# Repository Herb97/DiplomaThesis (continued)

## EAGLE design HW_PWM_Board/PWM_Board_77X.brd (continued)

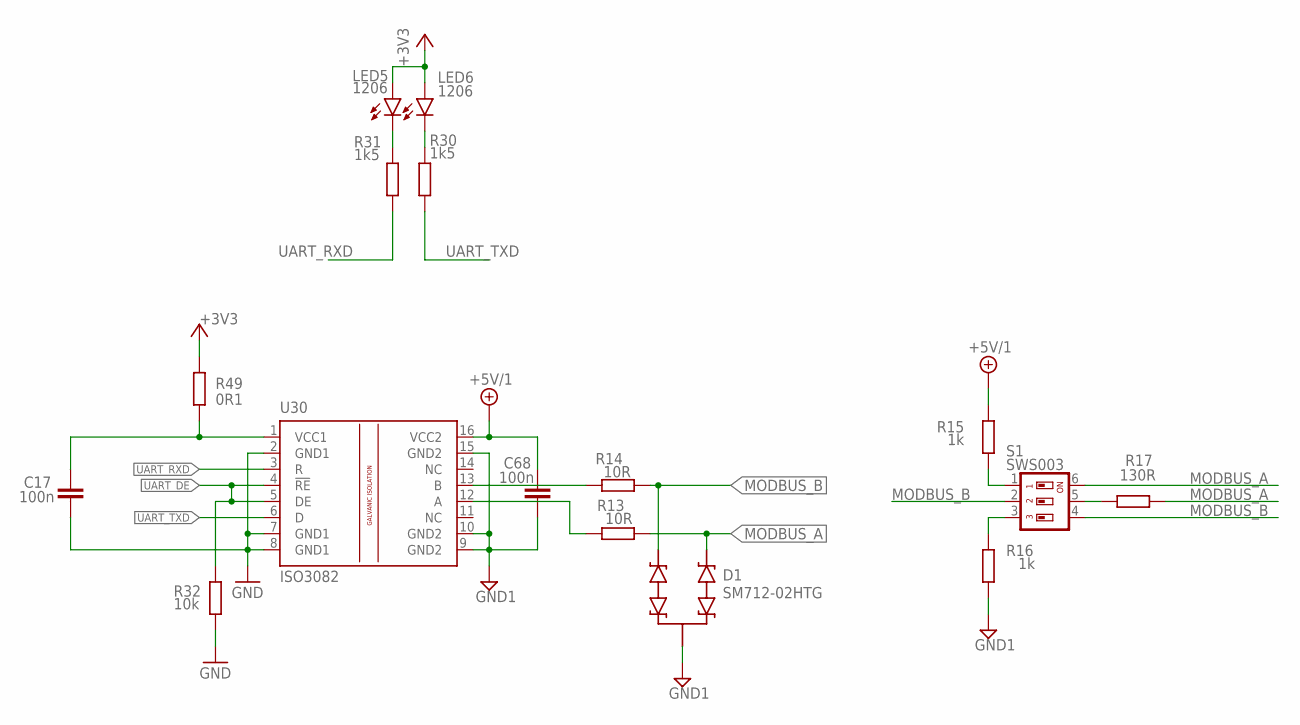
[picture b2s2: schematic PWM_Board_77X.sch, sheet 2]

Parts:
C17, C68: 100n; C0805
D1: SM712-02HTG; SOT23-BEC
LED5, LED6: 1206; CHIPLED_1206
R13, R14: 10R; R0603
R15, R16: 1k; R0603
R17: 130R; R1206
R30, R31: 1k5; R1206
R32: 10k; R0603
R49: 0R1; R1206
S1: SWS003; SMS-003
U30: ISO3082; SO-16DW

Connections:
+3V3: LED5.A, LED6.A, R49.2; also elsewhere on the board
+5V/1: C68.1, R15.2, U30.16 (VCC2); also elsewhere on the board
GND: C17.2, R32.1, U30.2 (GND1), U30.7 (GND1), U30.8 (GND1); also elsewhere on the board
GND1: C68.2, D1.C (E), R16.1, U30.9 (GND2), U30.10 (GND2), U30.15 (GND2); also elsewhere on the board
MODBUS_A: D1.E (2), R13.1, R17.1, S1.6; also elsewhere on the board
MODBUS_B: D1.B (1), R14.1, S1.2, S1.4; also elsewhere on the board
unnamed: R14.2, U30.13 (B)
unnamed: LED5.C, R31.1
unnamed: R13.2, U30.12 (A)
unnamed: R15.1, S1.1
unnamed: R16.2, S1.3
unnamed: R17.2, S1.5
unnamed: LED6.C, R30.1
unnamed: C17.1, R49.1, U30.1 (VCC1)
UART_DE: R32.2, U30.4 (!RE), U30.5 (DE); also elsewhere on the board
UART_RXD: R31.2, U30.3 (R); also elsewhere on the board
UART_TXD: R30.2, U30.6 (D); also elsewhere on the board

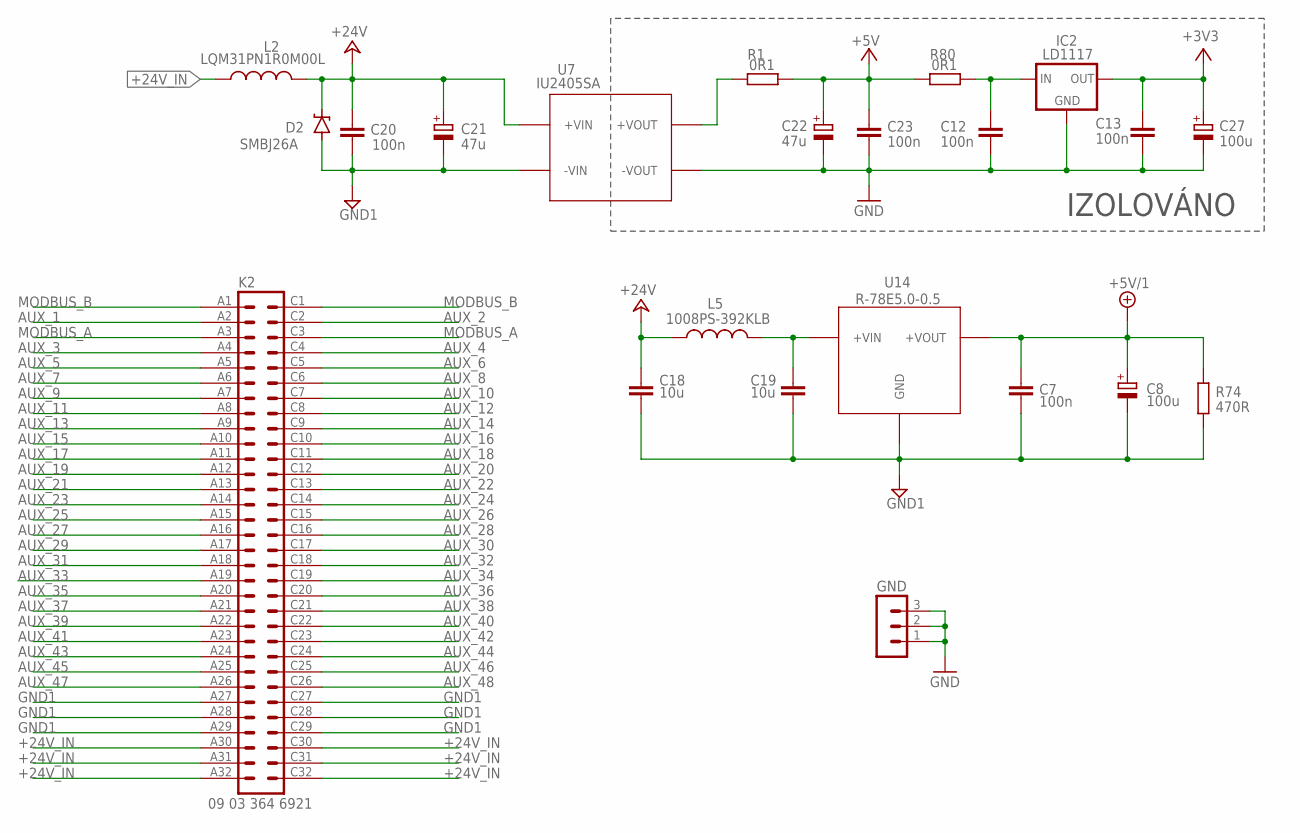
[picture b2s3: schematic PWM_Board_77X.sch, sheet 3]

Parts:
C7, C12, C13, C23: 100n; C0805
C8, C27: 100u; 153CLV-0605
C18, C19: 10u; C1206
C20: 100n; C1206
C21: 47u; E3,5-8
C22: 47u; 150CLZ-1014
D2: SMBJ26A; SMB
GND: MA03-1
IC2: LD1117; SOT223
K2: 09 03 364 6921; VG64P
L2: LQM31PN1R0M00L; R1206
L5: 1008PS-392KLB; L1812
R1, R80: 0R1; R1206
R74: 470R; R1206
U7: IU2405SA
U14: R-78C5.0-0.5; R-78E-0.5

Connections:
+3V3: C13.1, C27.+, IC2.2 (OUT); also elsewhere on the board
+5V: C22.+, C23.1, R1.2, R80.1; also elsewhere on the board
+5V/1: C7.1, C8.+, R74.2, U14.3 (+VOUT); also elsewhere on the board
+24V: C18.1, C20.1, C21.+, D2.C, L2.2, L5.1, U7.VIN+ (+VIN)
+24V_IN: K2.A30, K2.A31, K2.A32, K2.C30, K2.C31, K2.C32, L2.1
AUX_1: K2.A2
AUX_2: K2.C2
AUX_3: K2.A4
AUX_4: K2.C4
AUX_5: K2.A5
AUX_6: K2.C5
AUX_7: K2.A6
AUX_8: K2.C6
AUX_9: K2.A7
AUX_10: K2.C7
AUX_11: K2.A8
AUX_12: K2.C8
AUX_13: K2.A9
AUX_14: K2.C9
AUX_15: K2.A10
AUX_16: K2.C10
AUX_17: K2.A11
AUX_18: K2.C11
AUX_19: K2.A12
AUX_20: K2.C12
AUX_21: K2.A13
AUX_22: K2.C13
AUX_23: K2.A14
AUX_24: K2.C14
AUX_25: K2.A15
AUX_26: K2.C15
AUX_27: K2.A16
AUX_28: K2.C16
AUX_29: K2.A17
AUX_30: K2.C17
AUX_31: K2.A18
AUX_32: K2.C18
AUX_33: K2.A19
AUX_34: K2.C19
AUX_35: K2.A20
AUX_36: K2.C20
AUX_37: K2.A21
AUX_38: K2.C21
AUX_39: K2.A22
AUX_40: K2.C22
AUX_41: K2.A23
AUX_42: K2.C23
AUX_43: K2.A24
AUX_44: K2.C24
AUX_45: K2.A25
AUX_46: K2.C25
AUX_47: K2.A26
AUX_48: K2.C26
GND: C12.2, C13.2, C22.-, C23.2, C27.-, GND.1, GND.2, GND.3, IC2.1 (GND), U7.VOUT- (-VOUT); also elsewhere on the board
GND1: C7.2, C8.-, C18.2, C19.2, C20.2, C21.-, D2.A, K2.A27, K2.A28, K2.A29, K2.C27, K2.C28, K2.C29, R74.1, U7.VIN- (-VIN), U14.2 (GND); also elsewhere on the board
MODBUS_A: K2.A3, K2.C3; also elsewhere on the board
MODBUS_B: K2.A1, K2.C1; also elsewhere on the board
unnamed: R1.1, U7.VOUT+ (+VOUT)
unnamed: C12.1, IC2.3 (IN), R80.2
unnamed: C19.1, L5.2, U14.1 (+VIN)

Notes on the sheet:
IU2405SA
R-78E5.0-0.5
IZOLOVÁNO

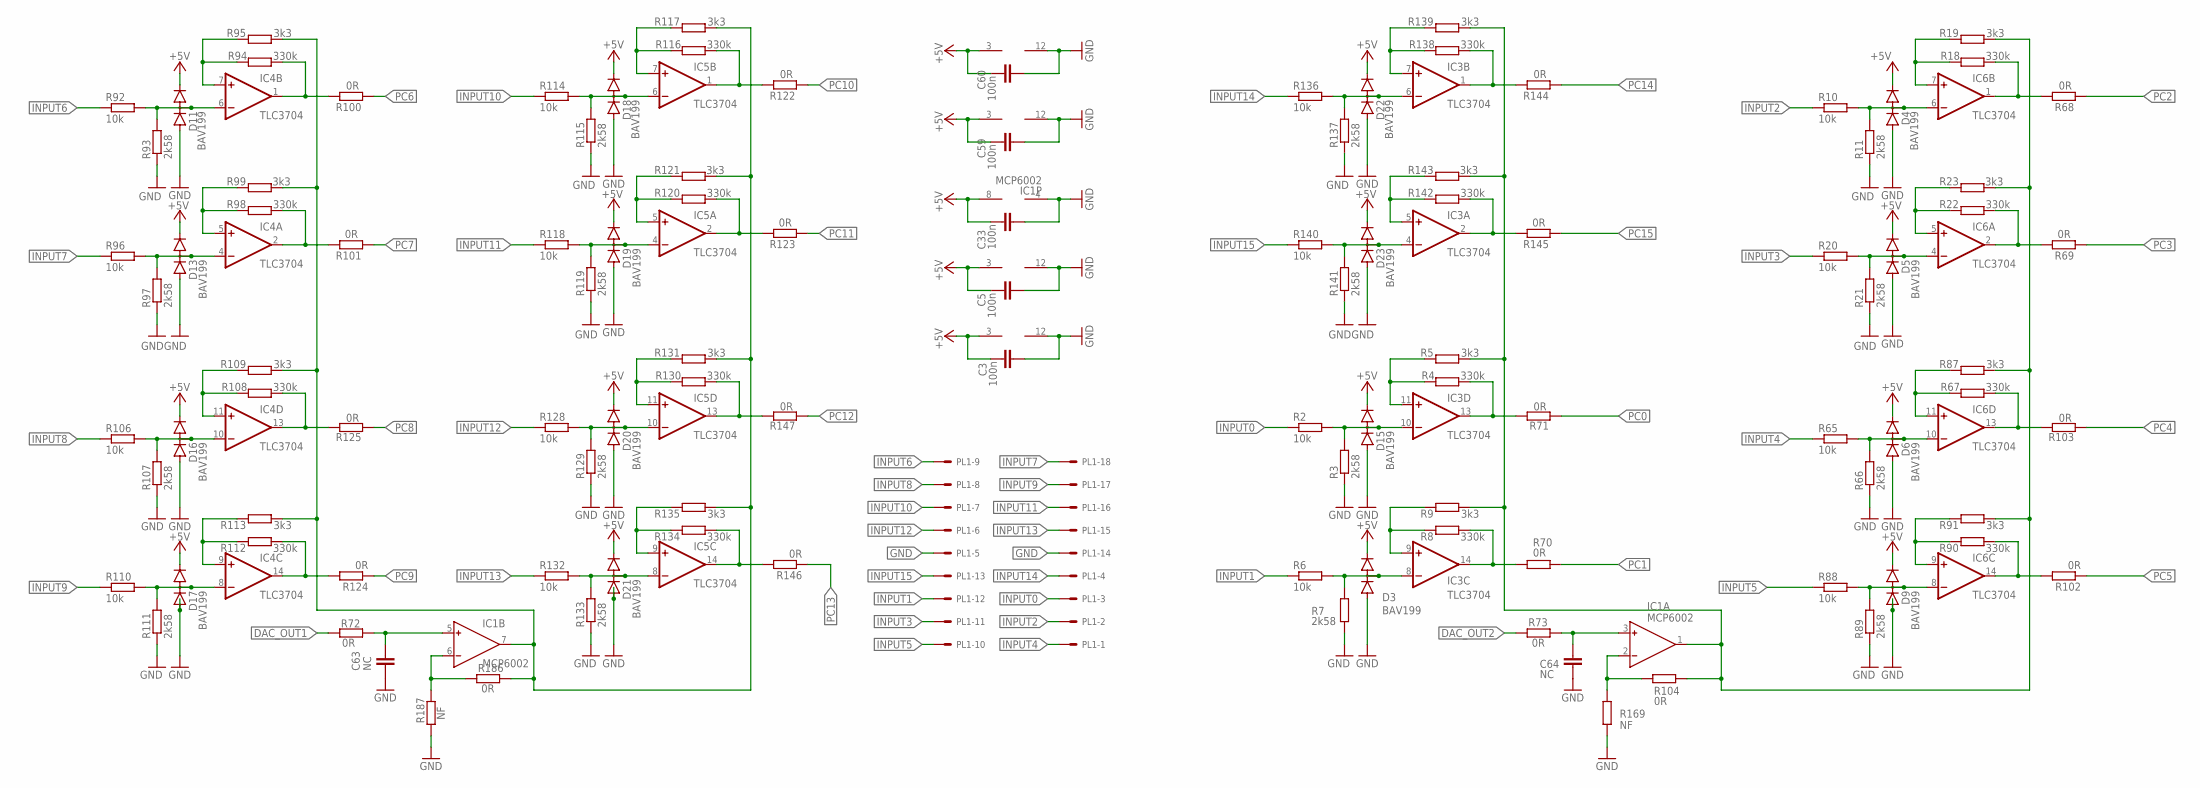
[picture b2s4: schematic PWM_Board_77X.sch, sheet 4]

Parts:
C3, C5, C33, C59, C60: 100n; C0805
C63, C64: NC; C0603
D3, D4, D5, D6, D9, D11, D13, D15, D16, D17, D18, D19, D20, D21, D22, D23: BAV199; SOT23
IC1: MCP6002; SO8
IC3, IC4, IC5, IC6: TLC3704; SO14
PL1: 555X-18H-NO-HOLES; 5569-18_NO_HOLES
R2, R6, R10, R20, R65, R88, R92, R96, R106, R110, R114, R118, R128, R132, R136, R140: 10k; R1206
R3, R7, R11, R21, R66, R89, R93, R97, R107, R111, R115, R119, R129, R133, R137, R141: 2k58; R0603
R4, R8, R18, R22, R67, R90, R94, R98, R108, R112, R116, R120, R130, R134, R138, R142: 330k; R0603
R5, R9, R19, R23, R87, R91, R95, R99, R109, R113, R117, R121, R131, R135, R139, R143: 3k3; R0603
R68, R69, R70, R71, R72, R73, R100, R101, R102, R103, R104, R122, R123, R124, R125, R144, R145, R146, R147, R186: 0R; R0603
R169, R187: NF; R0603

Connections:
+5V: C3.1, C5.1, C33.1, C59.1, C60.1, D3.2 (C), D4.2 (C), D5.2 (C), D6.2 (C), D9.2 (C), D11.2 (C), D13.2 (C), D15.2 (C), D16.2 (C), D17.2 (C), D18.2 (C), D19.2 (C), D20.2 (C), D21.2 (C), D22.2 (C), D23.2 (C), IC1.8 (V+), IC3.3 (V+), IC4.3 (V+), IC5.3 (V+), IC6.3 (V+); also elsewhere on the board
DAC_OUT1: R72.1; also elsewhere on the board
DAC_OUT2: R73.1; also elsewhere on the board
GND: C3.2, C5.2, C33.2, C59.2, C60.2, C63.2, C64.2, D3.1 (A), D4.1 (A), D5.1 (A), D6.1 (A), D9.1 (A), D11.1 (A), D13.1 (A), D15.1 (A), D16.1 (A), D17.1 (A), D18.1 (A), D19.1 (A), D20.1 (A), D21.1 (A), D22.1 (A), D23.1 (A), IC1.4 (V-), IC3.12 (V-), IC4.12 (V-), IC5.12 (V-), IC6.12 (V-), PL1.5, PL1.14, R3.1, R7.1, R11.1, R21.1, R66.1, R89.1, R93.1, R97.1, R107.1, R111.1, R115.1, R119.1, R129.1, R133.1, R137.1, R141.1, R169.1, R187.1; also elsewhere on the board
INPUT0: PL1.3, R2.1
INPUT1: PL1.12, R6.1
INPUT2: PL1.2, R10.1
INPUT3: PL1.11, R20.1
INPUT4: PL1.1, R65.1
INPUT5: PL1.10, R88.1
INPUT6: PL1.9, R92.1
INPUT7: PL1.18, R96.1
INPUT8: PL1.8, R106.1
INPUT9: PL1.17, R110.1
INPUT10: PL1.7, R114.1
INPUT11: PL1.16, R118.1
INPUT12: PL1.6, R128.1
INPUT13: PL1.15, R132.1
INPUT14: PL1.4, R136.1
INPUT15: PL1.13, R140.1
unnamed: IC3.11 (+IN), R4.2, R5.2
unnamed: D3.3 (AC), IC3.8 (-IN), R6.2, R7.2
unnamed: D15.3 (AC), IC3.10 (-IN), R2.2, R3.2
unnamed: IC3.9 (+IN), R8.2, R9.2
unnamed: D4.3 (AC), IC6.6 (-IN), R10.2, R11.2
unnamed: IC6.7 (+IN), R18.2, R19.2
unnamed: D5.3 (AC), IC6.4 (-IN), R20.2, R21.2
unnamed: IC6.5 (+IN), R22.2, R23.2
unnamed: IC1.6 (IN-), R186.1, R187.2
unnamed: C63.1, IC1.5 (IN+), R72.2
unnamed: IC6.1 (OUT), R18.1, R68.2
unnamed: C64.1, IC1.3 (IN+), R73.2
unnamed: IC6.2 (OUT), R22.1, R69.2
unnamed: IC1.2 (IN-), R104.1, R169.2
unnamed: IC1.7 (OUT), R95.1, R99.1, R109.1, R113.1, R117.1, R121.1, R131.1, R135.1, R186.2
unnamed: IC3.14 (OUT), R8.1, R70.2
unnamed: IC3.13 (OUT), R4.1, R71.2
unnamed: IC1.1 (OUT), R5.1, R9.1, R19.1, R23.1, R87.1, R91.1, R104.2, R139.1, R143.1
unnamed: D6.3 (AC), IC6.10 (-IN), R65.2, R66.2
unnamed: D9.3 (AC), IC6.8 (-IN), R88.2, R89.2
unnamed: IC6.9 (+IN), R90.2, R91.2
unnamed: D11.3 (AC), IC4.6 (-IN), R92.2, R93.2
unnamed: IC4.7 (+IN), R94.2, R95.2
unnamed: D13.3 (AC), IC4.4 (-IN), R96.2, R97.2
unnamed: IC4.5 (+IN), R98.2, R99.2
unnamed: IC6.11 (+IN), R67.2, R87.2
unnamed: IC4.1 (OUT), R94.1, R100.2
unnamed: IC4.2 (OUT), R98.1, R101.2
unnamed: IC6.14 (OUT), R90.1, R102.2
unnamed: IC6.13 (OUT), R67.1, R103.2
unnamed: D16.3 (AC), IC4.10 (-IN), R106.2, R107.2
unnamed: D17.3 (AC), IC4.8 (-IN), R110.2, R111.2
unnamed: IC4.9 (+IN), R112.2, R113.2
unnamed: D18.3 (AC), IC5.6 (-IN), R114.2, R115.2
unnamed: IC5.7 (+IN), R116.2, R117.2
unnamed: D19.3 (AC), IC5.4 (-IN), R118.2, R119.2
unnamed: IC5.5 (+IN), R120.2, R121.2
unnamed: IC4.11 (+IN), R108.2, R109.2
unnamed: IC5.1 (OUT), R116.1, R122.2
unnamed: IC5.2 (OUT), R120.1, R123.2
unnamed: IC4.14 (OUT), R112.1, R124.2
unnamed: IC4.13 (OUT), R108.1, R125.2
unnamed: D20.3 (AC), IC5.10 (-IN), R128.2, R129.2
unnamed: D21.3 (AC), IC5.8 (-IN), R132.2, R133.2
unnamed: IC5.9 (+IN), R134.2, R135.2
unnamed: D22.3 (AC), IC3.6 (-IN), R136.2, R137.2
unnamed: IC3.7 (+IN), R138.2, R139.2
unnamed: D23.3 (AC), IC3.4 (-IN), R140.2, R141.2
unnamed: IC3.5 (+IN), R142.2, R143.2
unnamed: IC5.11 (+IN), R130.2, R131.2
unnamed: IC3.1 (OUT), R138.1, R144.2
unnamed: IC3.2 (OUT), R142.1, R145.2
unnamed: IC5.14 (OUT), R134.1, R146.2
unnamed: IC5.13 (OUT), R130.1, R147.2
PC0: R71.1; also elsewhere on the board
PC1: R70.1; also elsewhere on the board
PC2: R68.1; also elsewhere on the board
PC3: R69.1; also elsewhere on the board
PC4: R103.1; also elsewhere on the board
PC5: R102.1; also elsewhere on the board
PC6: R100.1; also elsewhere on the board
PC7: R101.1; also elsewhere on the board
PC8: R125.1; also elsewhere on the board
PC9: R124.1; also elsewhere on the board
PC10: R122.1; also elsewhere on the board
PC11: R123.1; also elsewhere on the board
PC12: R147.1; also elsewhere on the board
PC13: R146.1; also elsewhere on the board
PC14: R144.1; also elsewhere on the board
PC15: R145.1; also elsewhere on the board

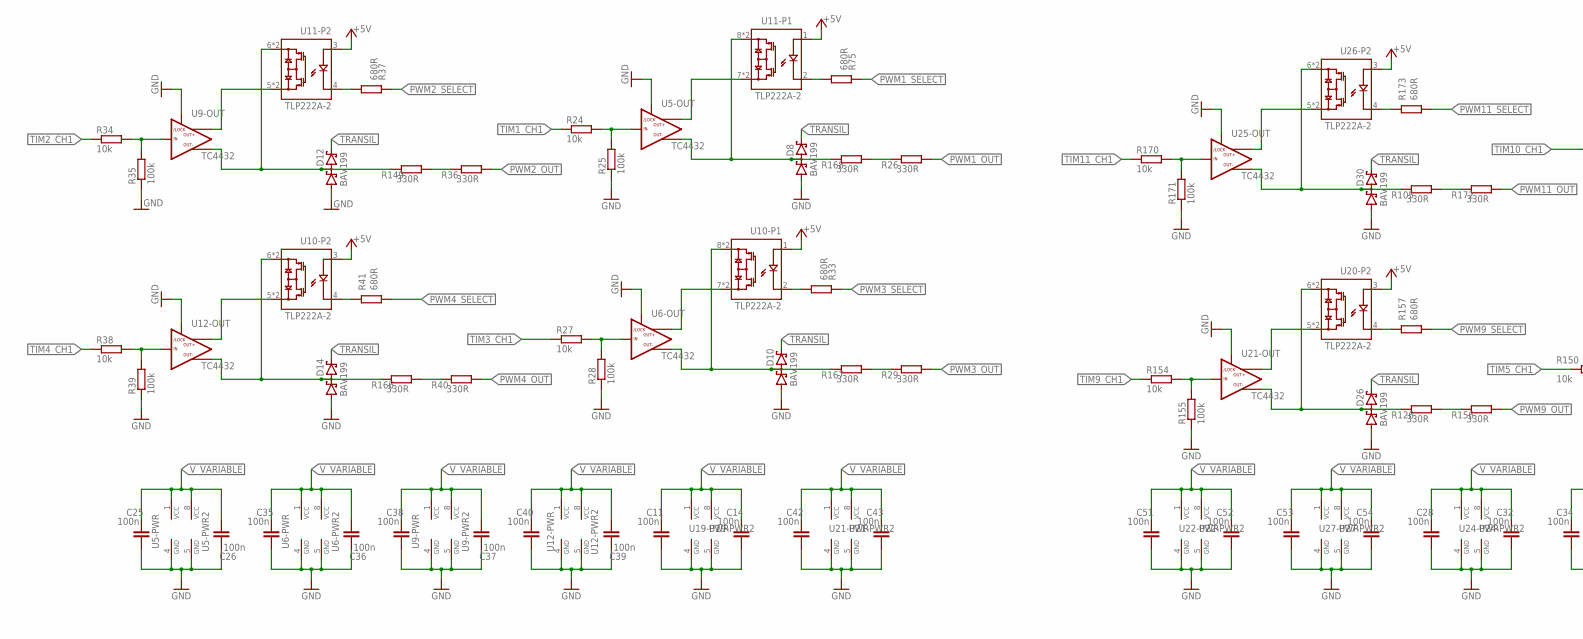
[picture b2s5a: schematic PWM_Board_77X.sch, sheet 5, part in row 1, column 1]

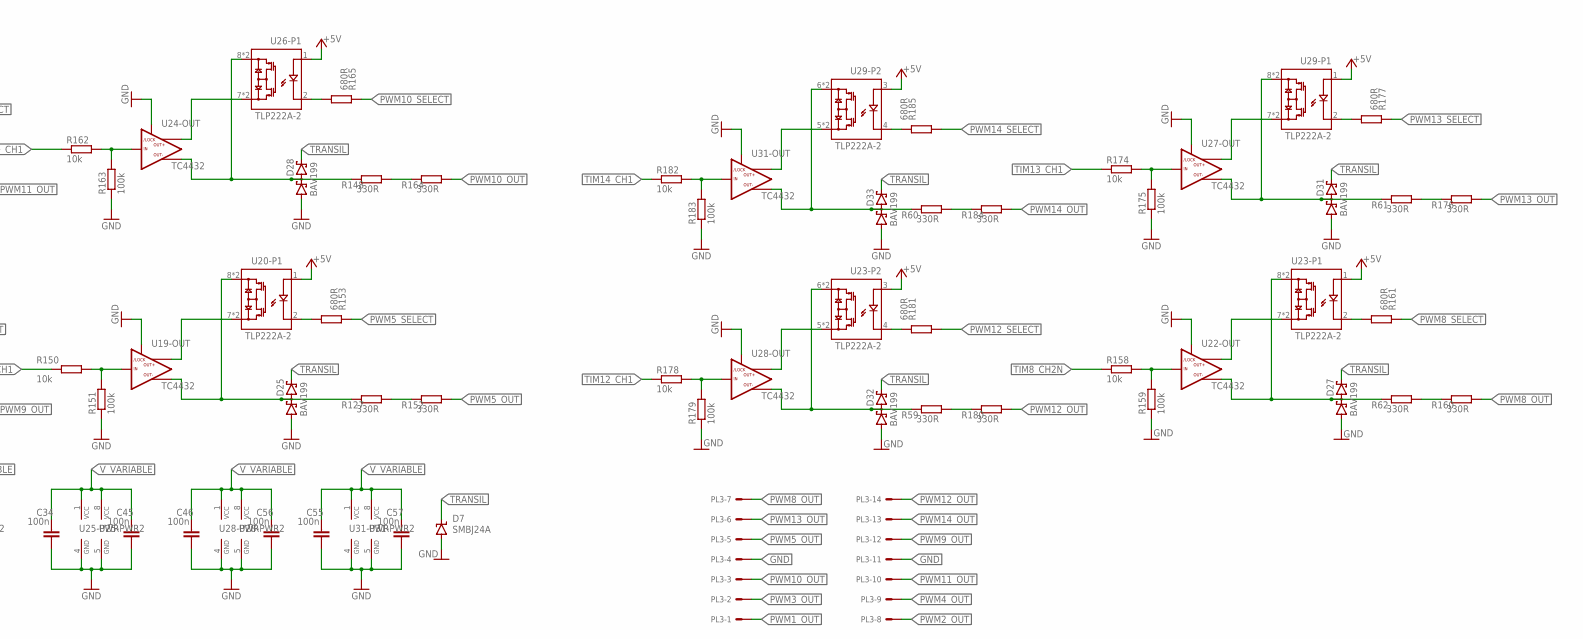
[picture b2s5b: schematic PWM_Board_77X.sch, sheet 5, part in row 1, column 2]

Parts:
C11, C14, C25, C26, C28, C32, C34, C35, C36, C37, C38, C39, C40, C42, C43, C45, C46, C51, C52, C53, C54, C55, C56, C57: 100n; C0805
D7: SMBJ24A; SMBJ
D8, D10, D12, D14, D25, D26, D27, D28, D30, D31, D32, D33: BAV199; SOT23
PL3: 555X-14H-NO-HOLES; 5569-14_NO_HOLES
R24, R27, R34, R38, R150, R154, R158, R162, R170, R174, R178, R182: 10k; R0603
R25, R28, R35, R39, R151, R155, R159, R163, R171, R175, R179, R183: 100k; R0603
R26, R29, R36, R40, R59, R60, R61, R62, R105, R126, R127, R148, R149, R152, R156, R160, R164, R166, R167, R168, R172, R176, R180, R184: 330R; R1210
R33, R37, R41, R75, R153, R157, R161, R165, R173, R177, R181, R185: 680R; R0603
U5, U6, U9, U12, U19, U21, U22, U24, U25, U27, U28, U31: TC4432; SO08
U10, U11, U20, U23, U26, U29: TLP222A-2; DIL8-SMD_V2

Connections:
+5V: U10.1 (A), U10.3 (A), U11.1 (A), U11.3 (A), U20.1 (A), U20.3 (A), U23.1 (A), U23.3 (A), U26.1 (A), U26.3 (A), U29.1 (A), U29.3 (A); also elsewhere on the board
GND: C11.2, C14.2, C25.2, C26.1, C28.2, C32.2, C34.2, C35.2, C36.1, C37.1, C38.2, C39.1, C40.2, C42.2, C43.2, C45.2, C46.2, C51.2, C52.2, C53.2, C54.2, C55.2, C56.2, C57.2, D7.A, D8.1 (A1), D10.1 (A1), D12.1 (A1), D14.1 (A1), D25.1 (A1), D26.1 (A1), D27.1 (A1), D28.1 (A1), D30.1 (A1), D31.1 (A1), D32.1 (A1), D33.1 (A1), PL3.4, PL3.11, R25.1, R28.1, R35.1, R39.1, R151.1, R155.1, R159.1, R163.1, R171.1, R175.1, R179.1, R183.1, U5.3 (/LOCK), U5.4 (GND), U5.5 (GND), U6.3 (/LOCK), U6.4 (GND), U6.5 (GND), U9.3 (/LOCK), U9.4 (GND), U9.5 (GND), U12.3 (/LOCK), U12.4 (GND), U12.5 (GND), U19.3 (/LOCK), U19.4 (GND), U19.5 (GND), U21.3 (/LOCK), U21.4 (GND), U21.5 (GND), U22.3 (/LOCK), U22.4 (GND), U22.5 (GND), U24.3 (/LOCK), U24.4 (GND), U24.5 (GND), U25.3 (/LOCK), U25.4 (GND), U25.5 (GND), U27.3 (/LOCK), U27.4 (GND), U27.5 (GND), U28.3 (/LOCK), U28.4 (GND), U28.5 (GND), U31.3 (/LOCK), U31.4 (GND), U31.5 (GND); also elsewhere on the board
unnamed: U5.7 (OUT+), U11.7 (O2), U11.10 (O2)
unnamed: U6.7 (OUT+), U10.7 (O2), U10.10 (O2)
unnamed: R24.2, R25.2, U5.2 (-IN)
unnamed: D8.3 (C1A2), R168.1, U5.6 (OUT-), U11.8 (O1), U11.9 (O1)
unnamed: R27.2, R28.2, U6.2 (-IN)
unnamed: R41.1, U10.4 (K)
unnamed: R33.1, U10.2 (K)
unnamed: R34.2, R35.2, U9.2 (-IN)
unnamed: R37.1, U11.4 (K)
unnamed: U10.5 (O2), U10.12 (O2), U12.7 (OUT+)
unnamed: R38.2, R39.2, U12.2 (-IN)
unnamed: D14.3 (C1A2), R166.1, U10.6 (O1), U10.11 (O1), U12.6 (OUT-)
unnamed: R75.1, U11.2 (K)
unnamed: R59.2, R180.1
unnamed: R60.2, R184.1
unnamed: D33.3 (C1A2), R60.1, U29.6 (O1), U29.11 (O1), U31.6 (OUT-)
unnamed: D10.3 (C1A2), R167.1, U6.6 (OUT-), U10.8 (O1), U10.9 (O1)
unnamed: R61.2, R176.1
unnamed: R62.2, R160.1
unnamed: R105.2, R172.1
unnamed: U19.7 (OUT+), U20.7 (O2), U20.10 (O2)
unnamed: R150.2, R151.2, U19.2 (-IN)
unnamed: D25.3 (C1A2), R127.1, U19.6 (OUT-), U20.8 (O1), U20.9 (O1)
unnamed: U20.5 (O2), U20.12 (O2), U21.7 (OUT+)
unnamed: R154.2, R155.2, U21.2 (-IN)
unnamed: U22.7 (OUT+), U23.7 (O2), U23.10 (O2)
unnamed: R158.2, R159.2, U22.2 (-IN)
unnamed: D27.3 (C1A2), R62.1, U22.6 (OUT-), U23.8 (O1), U23.9 (O1)
unnamed: U24.7 (OUT+), U26.7 (O2), U26.10 (O2)
unnamed: R162.2, R163.2, U24.2 (-IN)
unnamed: R153.1, U20.2 (K)
unnamed: R161.1, U23.2 (K)
unnamed: R126.2, R156.1
unnamed: R148.2, R164.1
unnamed: R127.2, R152.1
unnamed: R36.1, R149.2
unnamed: R157.1, U20.4 (K)
unnamed: D26.3 (C1A2), R126.1, U20.6 (O1), U20.11 (O1), U21.6 (OUT-)
unnamed: R165.1, U26.2 (K)
unnamed: D28.3 (C1A2), R148.1, U24.6 (OUT-), U26.8 (O1), U26.9 (O1)
unnamed: U25.7 (OUT+), U26.5 (O2), U26.12 (O2)
unnamed: R170.2, R171.2, U25.2 (-IN)
unnamed: D30.3 (C1A2), R105.1, U25.6 (OUT-), U26.6 (O1), U26.11 (O1)
unnamed: U27.7 (OUT+), U29.7 (O2), U29.10 (O2)
unnamed: R174.2, R175.2, U27.2 (-IN)
unnamed: U23.5 (O2), U23.12 (O2), U28.7 (OUT+)
unnamed: R178.2, R179.2, U28.2 (-IN)
unnamed: D32.3 (C1A2), R59.1, U23.6 (O1), U23.11 (O1), U28.6 (OUT-)
unnamed: U29.5 (O2), U29.12 (O2), U31.7 (OUT+)
unnamed: R182.2, R183.2, U31.2 (-IN)
unnamed: R173.1, U26.4 (K)
unnamed: R181.1, U23.4 (K)
unnamed: R40.1, R166.2
unnamed: R26.1, R168.2
unnamed: R177.1, U29.2 (K)
unnamed: D31.3 (C1A2), R61.1, U27.6 (OUT-), U29.8 (O1), U29.9 (O1)
unnamed: R185.1, U29.4 (K)
unnamed: R29.1, R167.2
unnamed: U9.7 (OUT+), U11.5 (O2), U11.12 (O2)
unnamed: D12.3 (C1A2), R149.1, U9.6 (OUT-), U11.6 (O1), U11.11 (O1)
PWM1_OUT: PL3.1, R26.2
PWM1_SELECT: R75.2; also elsewhere on the board
PWM2_OUT: PL3.8, R36.2
PWM2_SELECT: R37.2; also elsewhere on the board
PWM3_OUT: PL3.2, R29.2
PWM3_SELECT: R33.2; also elsewhere on the board
PWM4_OUT: PL3.9, R40.2
PWM4_SELECT: R41.2; also elsewhere on the board
PWM5_OUT: PL3.5, R152.2
PWM5_SELECT: R153.2; also elsewhere on the board
PWM8_OUT: PL3.7, R160.2
PWM8_SELECT: R161.2; also elsewhere on the board
PWM9_OUT: PL3.12, R156.2
PWM9_SELECT: R157.2; also elsewhere on the board
PWM10_OUT: PL3.3, R164.2
PWM10_SELECT: R165.2; also elsewhere on the board
PWM11_OUT: PL3.10, R172.2
PWM11_SELECT: R173.2; also elsewhere on the board
PWM12_OUT: PL3.14, R180.2
PWM12_SELECT: R181.2; also elsewhere on the board
PWM13_OUT: PL3.6, R176.2
PWM13_SELECT: R177.2; also elsewhere on the board
PWM14_OUT: PL3.13, R184.2
PWM14_SELECT: R185.2; also elsewhere on the board
TIM1_CH1: R24.1; also elsewhere on the board
TIM2_CH1: R34.1; also elsewhere on the board
TIM3_CH1: R27.1; also elsewhere on the board
TIM4_CH1: R38.1; also elsewhere on the board
TIM5_CH1: R150.1; also elsewhere on the board
TIM8_CH2N: R158.1; also elsewhere on the board
TIM9_CH1: R154.1; also elsewhere on the board
TIM10_CH1: R162.1; also elsewhere on the board
TIM11_CH1: R170.1; also elsewhere on the board
TIM12_CH1: R178.1; also elsewhere on the board
TIM13_CH1: R174.1; also elsewhere on the board
TIM14_CH1: R182.1; also elsewhere on the board
TRANSIL: D7.C, D8.2 (C2), D10.2 (C2), D12.2 (C2), D14.2 (C2), D25.2 (C2), D26.2 (C2), D27.2 (C2), D28.2 (C2), D30.2 (C2), D31.2 (C2), D32.2 (C2), D33.2 (C2)
V_VARIABLE: C11.1, C14.1, C25.1, C26.2, C28.1, C32.1, C34.1, C35.1, C36.2, C37.2, C38.1, C39.2, C40.1, C42.1, C43.1, C45.1, C46.1, C51.1, C52.1, C53.1, C54.1, C55.1, C56.1, C57.1, U5.1 (VCC), U5.8 (VCC), U6.1 (VCC), U6.8 (VCC), U9.1 (VCC), U9.8 (VCC), U12.1 (VCC), U12.8 (VCC), U19.1 (VCC), U19.8 (VCC), U21.1 (VCC), U21.8 (VCC), U22.1 (VCC), U22.8 (VCC), U24.1 (VCC), U24.8 (VCC), U25.1 (VCC), U25.8 (VCC), U27.1 (VCC), U27.8 (VCC), U28.1 (VCC), U28.8 (VCC), U31.1 (VCC), U31.8 (VCC); also elsewhere on the board

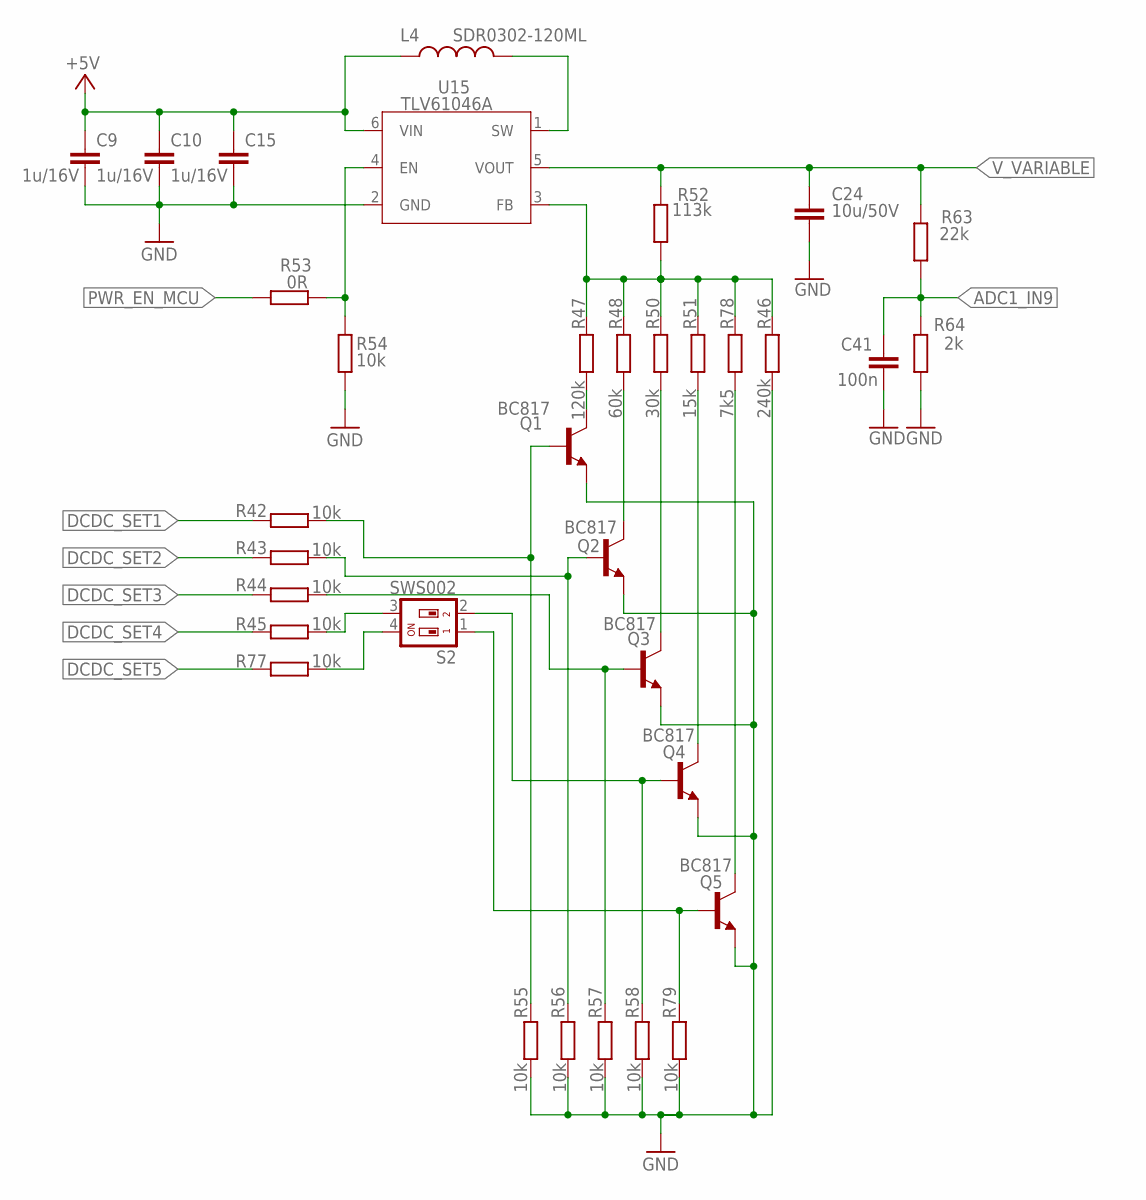
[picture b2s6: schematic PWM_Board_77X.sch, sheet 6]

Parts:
C9, C10, C15: 1u/16V; C0805
C24: 10u/50V; C1206
C41: 100n; C0805
L4: SDR0302-120ML; IND_NPI43C
Q1, Q2, Q3, Q4, Q5: BC817; SOT23-BEC
R42, R43, R44, R45, R54, R55, R56, R57, R58, R77, R79: 10k; R0603
R46: 240k; R0603
R47: 120k; R0603
R48: 60k; R0603
R50: 30k; R0603
R51: 15k; R0603
R52: 113k; R0603
R53: 0R; R0603
R63: 22k; R0603
R64: 2k; R0603
R78: 7k5; R0603
S2: SWS002; SMS-002
U15: TLV61046A; SOT23-6

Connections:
+5V: C9.1, C10.1, C15.1, L4.1, U15.6 (VIN); also elsewhere on the board
ADC1_IN9: C41.1, R63.1, R64.2; also elsewhere on the board
DCDC_SET1: R42.1; also elsewhere on the board
DCDC_SET2: R43.1; also elsewhere on the board
DCDC_SET3: R44.1; also elsewhere on the board
DCDC_SET4: R45.1; also elsewhere on the board
DCDC_SET5: R77.1; also elsewhere on the board
GND: C9.2, C10.2, C15.2, C24.2, C41.2, Q1.E, Q2.E, Q3.E, Q4.E, Q5.E, R46.1, R54.2, R55.2, R56.2, R57.2, R58.2, R64.1, R79.2, U15.2 (GND); also elsewhere on the board
unnamed: R77.2, S2.4
unnamed: R46.2, R47.2, R48.2, R50.2, R51.2, R52.1, R78.2, U15.3 (FB)
unnamed: Q2.C, R48.1
unnamed: Q3.C, R50.1
unnamed: Q4.C, R51.1
unnamed: Q1.C, R47.1
unnamed: Q2.B, R43.2, R56.1
unnamed: Q4.B, R58.1, S2.2
unnamed: R45.2, S2.3
unnamed: Q3.B, R44.2, R57.1
unnamed: Q1.B, R42.2, R55.1
unnamed: R53.1, R54.1, U15.4 (EN)
unnamed: L4.2, U15.1 (SW)
unnamed: Q5.C, R78.1
unnamed: Q5.B, R79.1, S2.1
PWR_EN_MCU: R53.2; also elsewhere on the board
V_VARIABLE: C24.1, R52.2, R63.2, U15.5 (VOUT); also elsewhere on the board

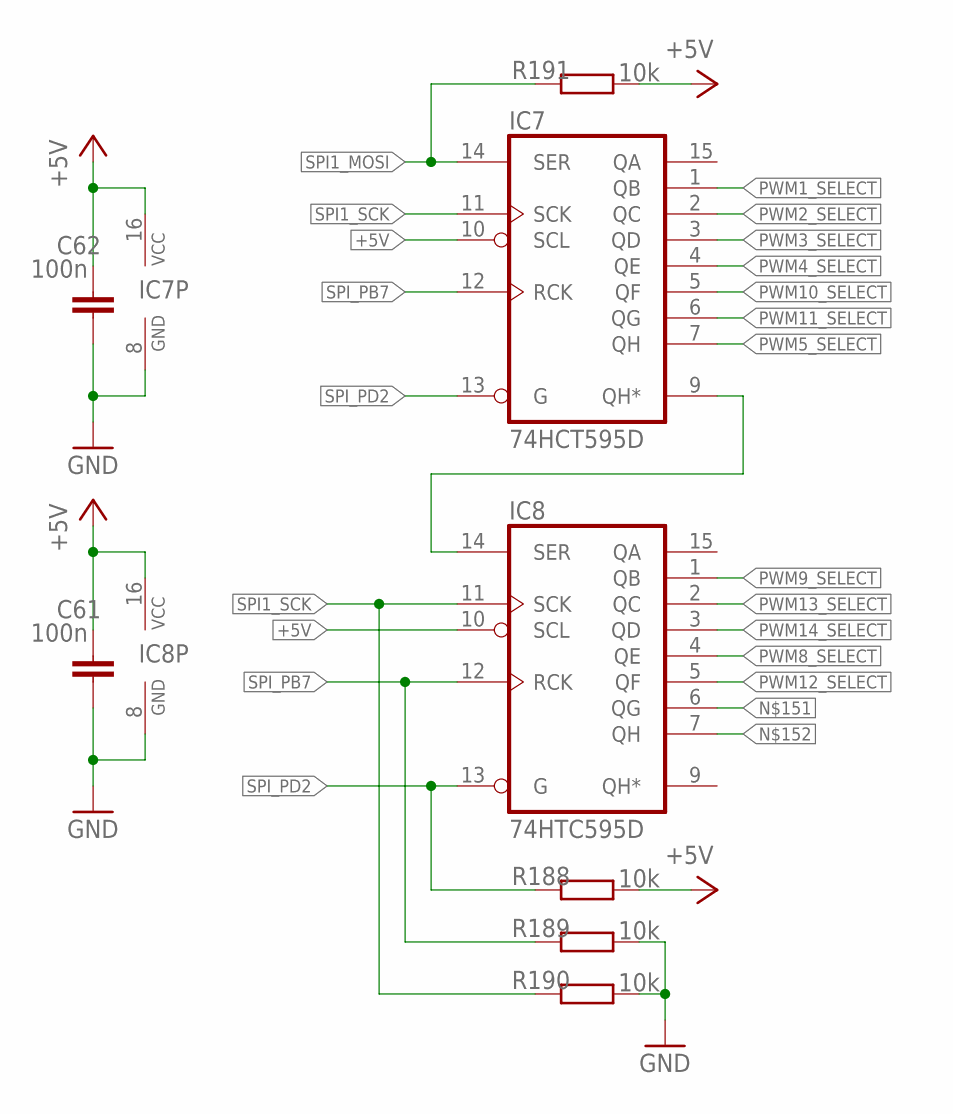
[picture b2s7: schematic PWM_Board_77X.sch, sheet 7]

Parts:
C61, C62: 100n; C0805
IC7: 74HCT595D; SO16
IC8: 74HTC595D; SO16
R188, R189, R190, R191: 10k; R0603

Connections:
+5V: C61.1, C62.1, IC7.10 (SCL), IC7.16 (VCC), IC8.10 (SCL), IC8.16 (VCC), R188.2, R191.2; also elsewhere on the board
GND: C61.2, C62.2, IC7.8 (GND), IC8.8 (GND), R189.2, R190.2; also elsewhere on the board
unnamed: IC7.9 (QH*), IC8.14 (SER)
PWM1_SELECT: IC7.1 (QB); also elsewhere on the board
PWM2_SELECT: IC7.2 (QC); also elsewhere on the board
PWM3_SELECT: IC7.3 (QD); also elsewhere on the board
PWM4_SELECT: IC7.4 (QE); also elsewhere on the board
PWM5_SELECT: IC7.7 (QH); also elsewhere on the board
PWM8_SELECT: IC8.4 (QE); also elsewhere on the board
PWM9_SELECT: IC8.1 (QB); also elsewhere on the board
PWM10_SELECT: IC7.5 (QF); also elsewhere on the board
PWM11_SELECT: IC7.6 (QG); also elsewhere on the board
PWM12_SELECT: IC8.5 (QF); also elsewhere on the board
PWM13_SELECT: IC8.2 (QC); also elsewhere on the board
PWM14_SELECT: IC8.3 (QD); also elsewhere on the board
SPI1_MOSI: IC7.14 (SER), R191.1; also elsewhere on the board
SPI1_SCK: IC7.11 (SCK), IC8.11 (SCK), R190.1; also elsewhere on the board
SPI_PB7: IC7.12 (RCK), IC8.12 (RCK), R189.1; also elsewhere on the board
SPI_PD2: IC7.13 (G), IC8.13 (G), R188.1; also elsewhere on the board

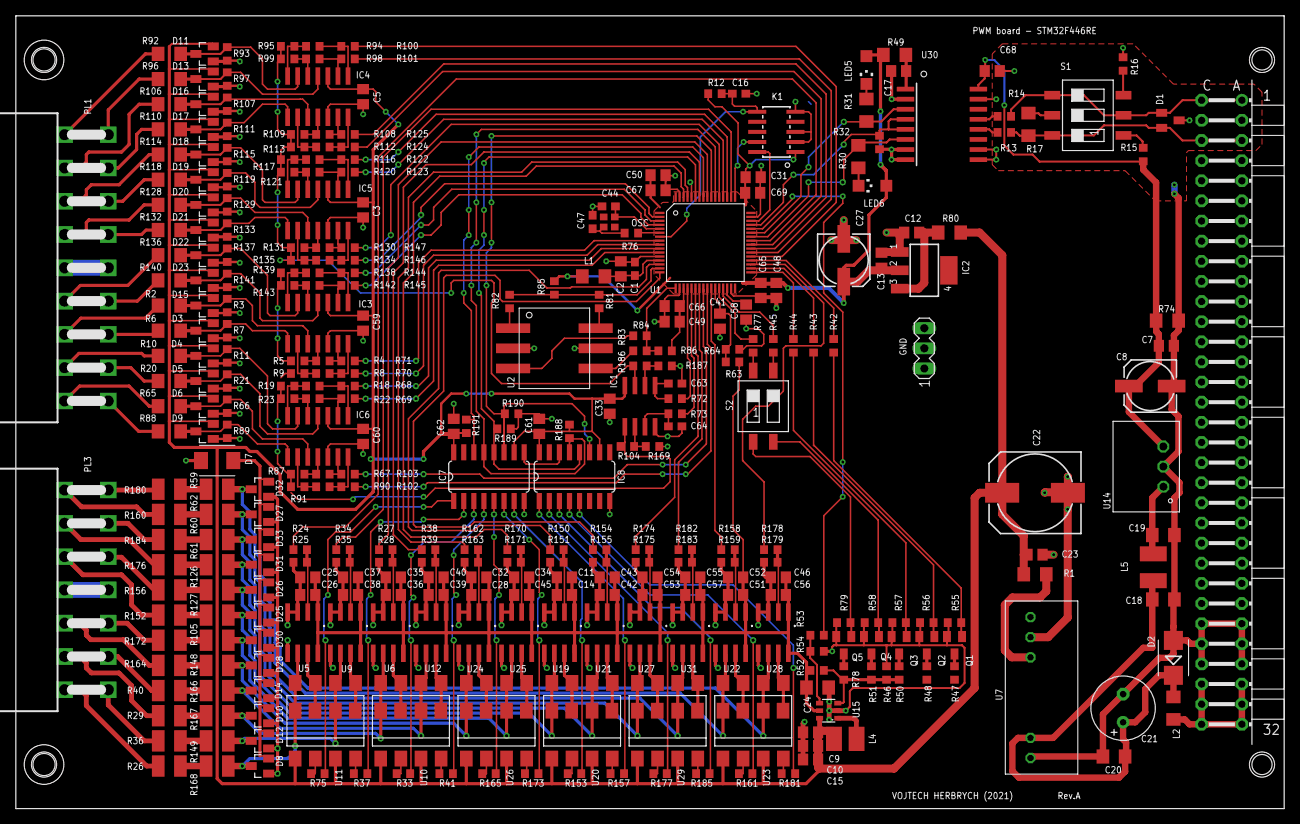
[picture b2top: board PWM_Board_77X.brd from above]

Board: 2 copper layers, 160.0 x 100.0 mm, 338 parts (0 on the bottom side), 250 nets.

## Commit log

2022-05-25 The attachment of Diploma Thesis added
